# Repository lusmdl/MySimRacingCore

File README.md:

# Sim Racing Core Controller

Welcome to the Sim Racing Core Controller repository!

This project focuses on programming the ATmega32u4 microcontroller to serve as the core of a high-performance sim racing setup. 
The controller independently handles all tasks, including steering, pedals, and accessory management, ensuring a streamlined and immersive racing experience—all without external setup software.

Other projects require PC-based software. 
This solution does everything directly on the microcontroller. 
Sensor calibration, configuration, and adjustments are all handled locally and stored in the microcontroller’s memory. 
The system can be operated intuitively via a simple interface.

This repository is designed to prioritize simplicity and reliability, with clean, maintainable code that’s easy to understand and adapt to your needs.

## Features

- 32 buttons (includes joystick button (1) for setup)
- Steering-Axis without FFB (Steering)
- Accelerate-Axis
- Brake-Axis
- X-Rotation-Axis (Joystick)
- Y-Rotation-Axis (Joystick)

## Getting Started

### Hardware Requirements

- **ATmega32u4 Microcontroller**: I use the original arduino micro board
- **Steering Wheel**: I use a cheap optical encoder with A and B line from china
- **Pedals**: I use a old xbox360 racing wheel pedal set. It only needs to work with potis.
- **Buttons**: The microcontroller get the 16 bit data from I2C Interface Adress 8 & 9 button data. You need a diffrent device for this. Look at my other project [here](https://github.com/lusmdl/MySimRacingButtonBox)!
- **Joystick**: I use a "normal" joystick from the Sony DualShock series and have designed a custom PCB to integrate it seamlessly. Special thanks to [little-scale](https://github.com/little-scale) for providing the [PS4 joystick footprint](https://github.com/little-scale/PS4_joystick_footprint), which served as the foundation for my design.
- **LCD**: I use a Arduino Uno with a LCD 2x16 shield. Look at this project [here](https://github.com/lusmdl/MySimRacingSetupDisplay).

> Example PCBs for this project

### Software Requirements

- [**Platform IO**](https://platformio.org/install/ide?install=vscode): Used for programming the ATmega32u4 microcontroller.
- [**AVR Lib**](https://github.com/avrdudes/avr-libc.git): standard lib for programming atmega microcontrollers with platformIO.
- [**Arduino AVR Core**](https://github.com/arduino/ArduinoCore-avr.git): used `Arduino.h`, `Wire.h` and `EEPROM.h`
- [**Arduino Joystick With Force Feedback Library**](https://github.com/YukMingLaw/ArduinoJoystickWithFFBLibrary.git): used for USB communication with the game

### Software Installation and Setup

> You can use the pre compiled hex file. Or you compile it yourself.

1. **Install PlatformIO**:
- Follow the [installation guide](https://platformio.org/install) to set up PlatformIO in your preferred environment (VSCode, Atom, etc.).

2. **Clone the Repository**:

```sh
git clone https://github.com/lusmdl/MySimRacingCore.git
```

3. **Open the Project**:
- Open the cloned repository folder in your PlatformIO environment.

4. **Build and Upload**:
- Connect your Arduino Micro.
- Build and upload the code using PlatformIO:

```sh
pio run --target upload
```

### Hardware Setup

To get started, you’ll need to assemble the accessories and adapt them to the Arduino Micro.

Special attention is required for the I2C interface and the encoder, as proper pull-up resistors are essential for reliable operation. 
To simplify this process, I’ve designed a custom PCB that integrates the Arduino Micro with all necessary accessories and I2C clients.

## Usage

1. **Connecting the Hardware**:
- Connect the accessorys to the Arduino Micro as per your configuration.
- Connect the Arduino Micro to the PC.

2. **Running the Code**:
- Power up your setup.
- The Arduino Micro will continuously push the accessorys states and update the Game data via USB.

3. **Setup the Wheelebase**
- Hit the joystick butten while booting..
- follow the instructions on the lcd

4. **Start your game and try it**

5. **Give feedback and report bugs**

## Documentation
- **Software**: [doc/software/html/index.html](/doc/software/html/index.html)

## Contributing

We welcome contributions from the community!

First, read the [general contributing conventions for projects from me](CONTRIBUTING.md).

1. Fork the repository.
2. Create a new branch (`git checkout -b feature-branch`).
3. Commit your changes (`git commit -am 'Add new feature'`).
4. Push to the branch (`git push origin feature-branch`).
5. Create a new Pull Request.

## License

This project is licensed under the MIT License - see the [LICENSE](LICENSE) file for details.

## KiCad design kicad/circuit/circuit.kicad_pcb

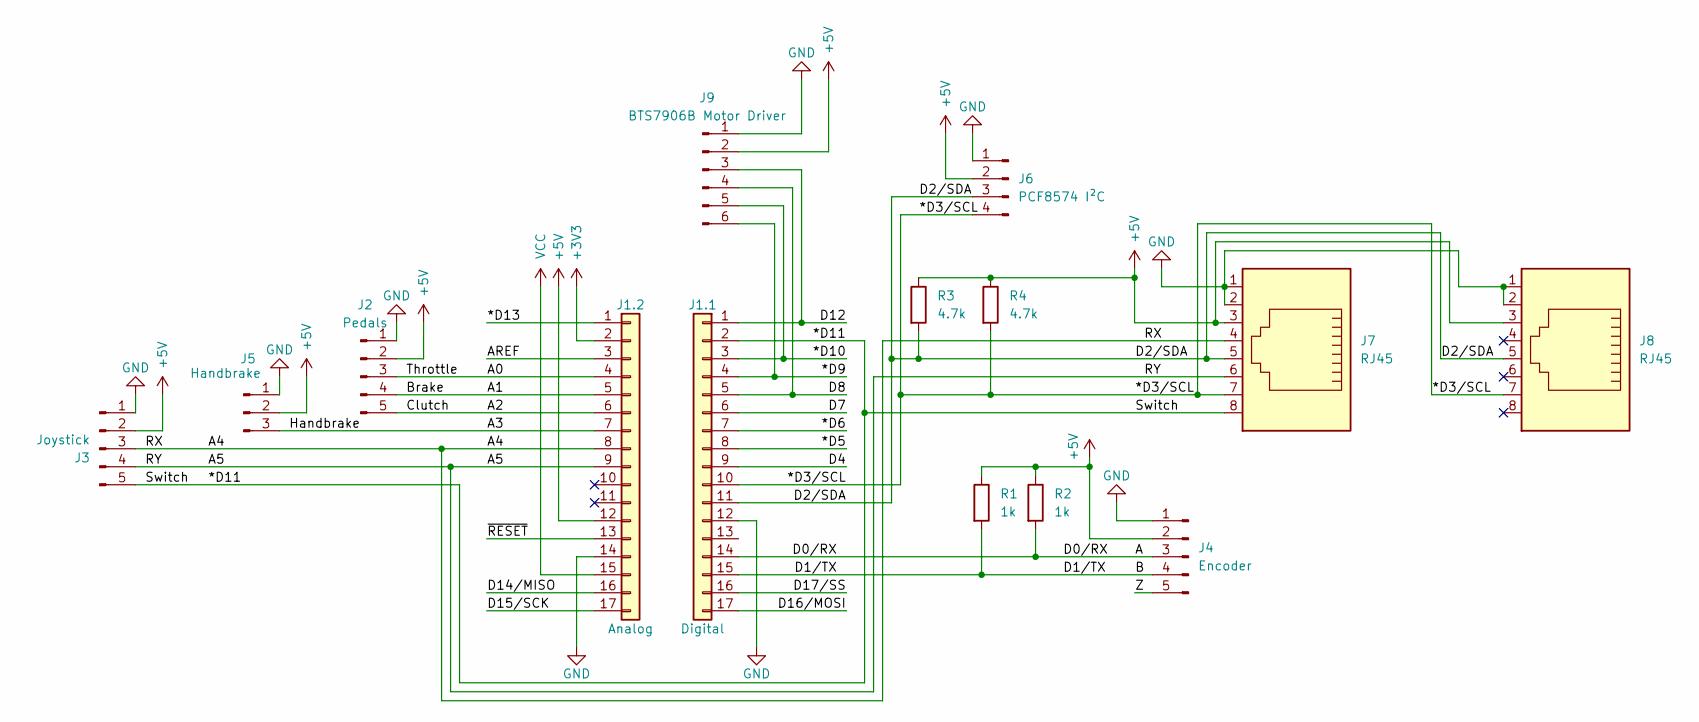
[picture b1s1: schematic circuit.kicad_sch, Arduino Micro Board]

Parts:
J1.1: Digital; PinSocket_1x17_P2.54mm_Vertical_SMD_Pin1Left
J1.2: Analog; PinSocket_1x17_P2.54mm_Vertical_SMD_Pin1Left
J2: Pedals; PinHeader_2x03_P2.54mm_Vertical_SMD
J3: Joystick; PinHeader_2x03_P2.54mm_Vertical_SMD
J4: Encoder; PinHeader_2x03_P2.54mm_Vertical_SMD
J5: Handbrake; PinHeader_2x02_P2.54mm_Vertical_SMD
J6: PCF8574 I²C; PinHeader_2x02_P2.54mm_Vertical_SMD
J7, J8: RJ45; RJ45_Molex_0855135013_Vertical
J9: BTS7906B Motor Driver; PinHeader_2x03_P2.54mm_Vertical_SMD
R1, R2: 1k; R_0402_1005Metric
R3, R4: 4.7k; R_0402_1005Metric

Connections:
+3V3: J1.2.2
+5V: J1.2.12, J2.2, J3.2, J4.2, J5.2, J6.2, J7.3, J8.3, J9.2, R1.1, R2.1, R3.1, R4.1
/*D3/SCL: J1.1.10, J6.4, J7.7, J8.7, R4.2
/*D5: J1.1.8
/*D6: J1.1.7
/*D9: J1.1.4, J9.6
/*D10: J1.1.3, J9.5
/*D11: J1.1.2, J3.5, J7.8
/*D13: J1.2.1
/A: J1.1.14, J4.3, R2.2
/A0: J1.2.4, J2.3
/A1: J1.2.5, J2.4
/A2: J1.2.6, J2.5
/A3: J1.2.7, J5.3
/A4: J1.2.8, J3.3, J7.4
/A5: J1.2.9, J3.4, J7.6
/AREF: J1.2.3
/B: J1.1.15, J4.4, R1.2
/D2/SDA: J1.1.11, J6.3, J7.5, J8.5, R3.2
/D4: J1.1.9
/D7: J1.1.6
/D8: J1.1.5, J9.4
/D12: J1.1.1, J9.3
/D14/MISO: J1.2.16
/D15/SCK: J1.2.17
/D16/MOSI: J1.1.17
/D17/SS: J1.1.16
/Z: J4.5
/~RESET: J1.2.13
GND: J1.1.12, J1.2.14, J2.1, J3.1, J4.1, J5.1, J6.1, J7.1, J7.2, J8.1, J8.2, J9.1
VCC: J1.2.15

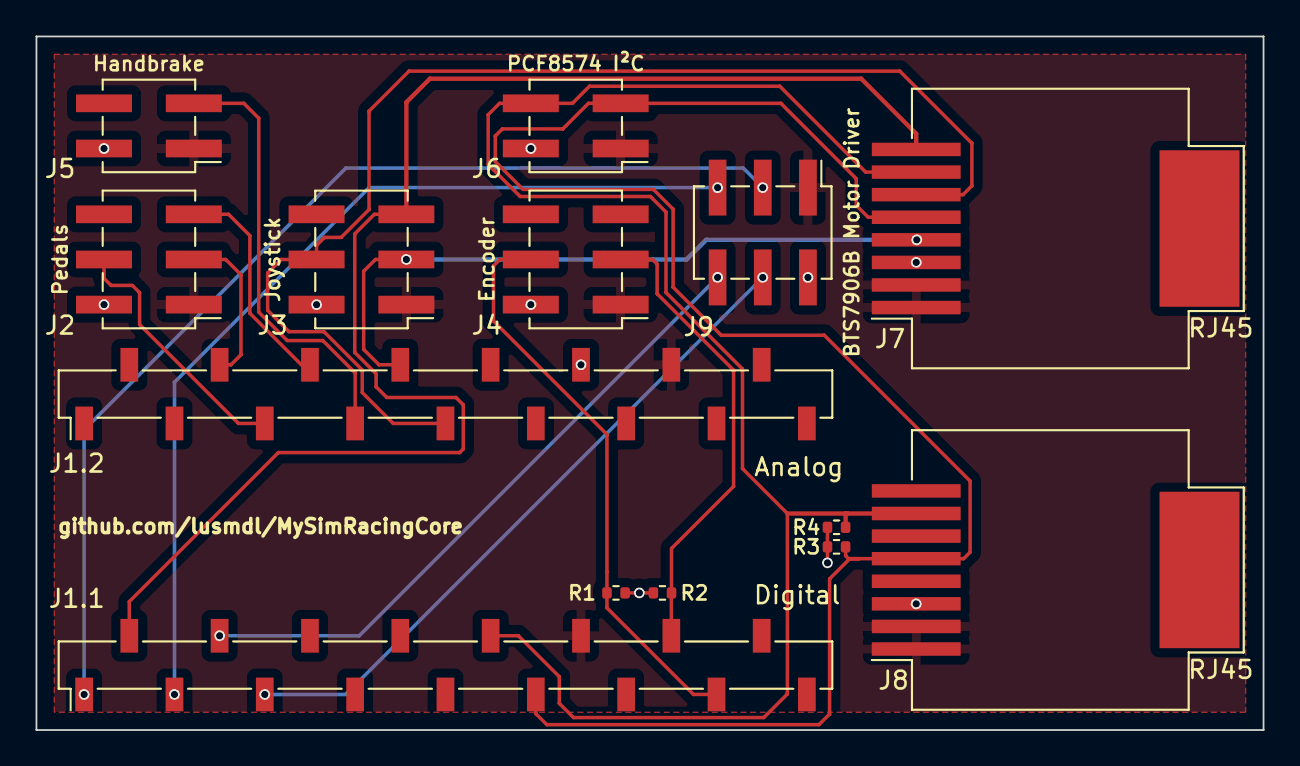
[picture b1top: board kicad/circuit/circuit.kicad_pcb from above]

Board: 2 copper layers, 69.0 x 39.0 mm, 14 parts (0 on the bottom side), 17 nets.

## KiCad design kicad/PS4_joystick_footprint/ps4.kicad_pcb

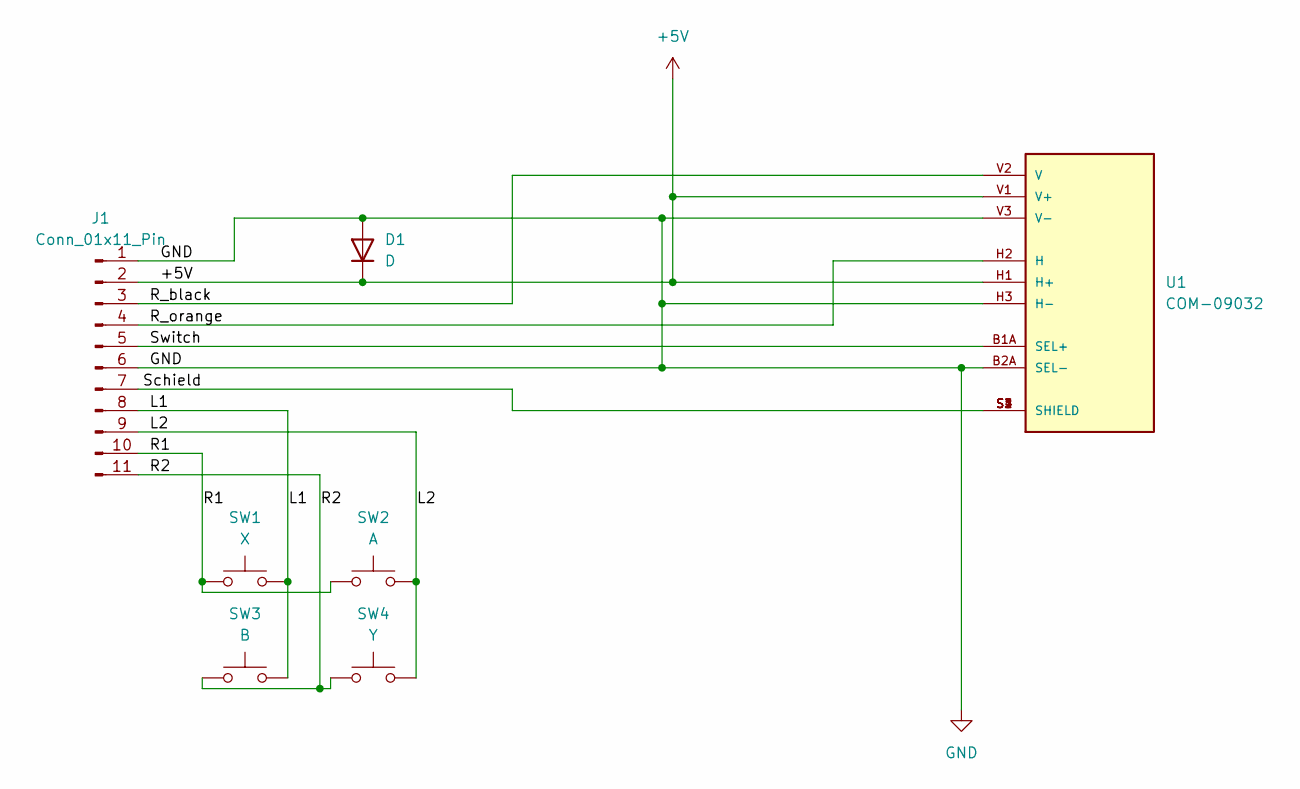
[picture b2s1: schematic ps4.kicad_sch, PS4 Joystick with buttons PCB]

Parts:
D1: D; D_MiniMELF
J1: Conn_01x11_Pin; PinHeader_1x11_P2.54mm_Vertical
SW1: X; SW_SPST_B3S-1000
SW2: A; SW_SPST_B3S-1000
SW3: B; SW_SPST_B3S-1000
SW4: Y; SW_SPST_B3S-1000
U1: COM-09032; PS4_joystick; PARTREV N/A

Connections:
+5V: D1.1 (K), J1.2, U1.H1 (H+), U1.V1 (V+)
/L1: J1.8, SW1.2, SW3.2
/L2: J1.9, SW2.2, SW4.2
/R1: J1.10, SW1.1, SW2.1
/R2: J1.11, SW3.1, SW4.1
/R_black: J1.3, U1.V2 (V)
/R_orange: J1.4, U1.H2 (H)
/Schield: J1.7, U1.S1 (SHIELD), U1.S2 (SHIELD), U1.S3 (SHIELD), U1.S4 (SHIELD)
/Switch: J1.5, U1.B1A (SEL+)
GND: D1.2 (A), J1.1, J1.6, U1.B2A (SEL-), U1.H3 (H-), U1.V3 (V-)

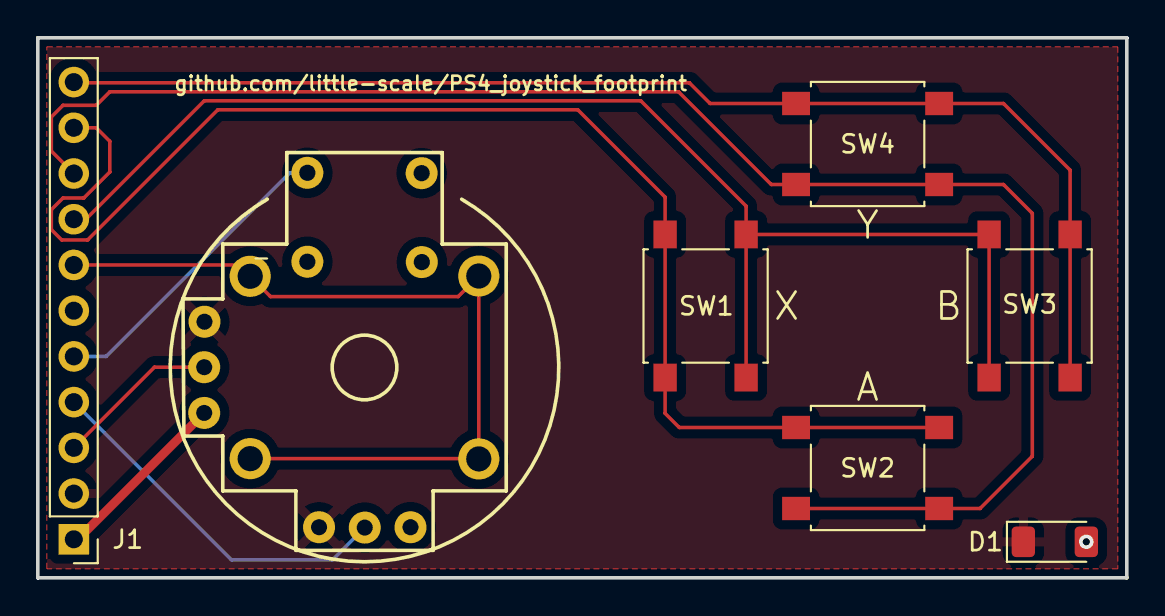
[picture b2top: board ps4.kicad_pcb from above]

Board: 2 copper layers, 60.5 x 30.0 mm, 7 parts (0 on the bottom side), 10 nets.

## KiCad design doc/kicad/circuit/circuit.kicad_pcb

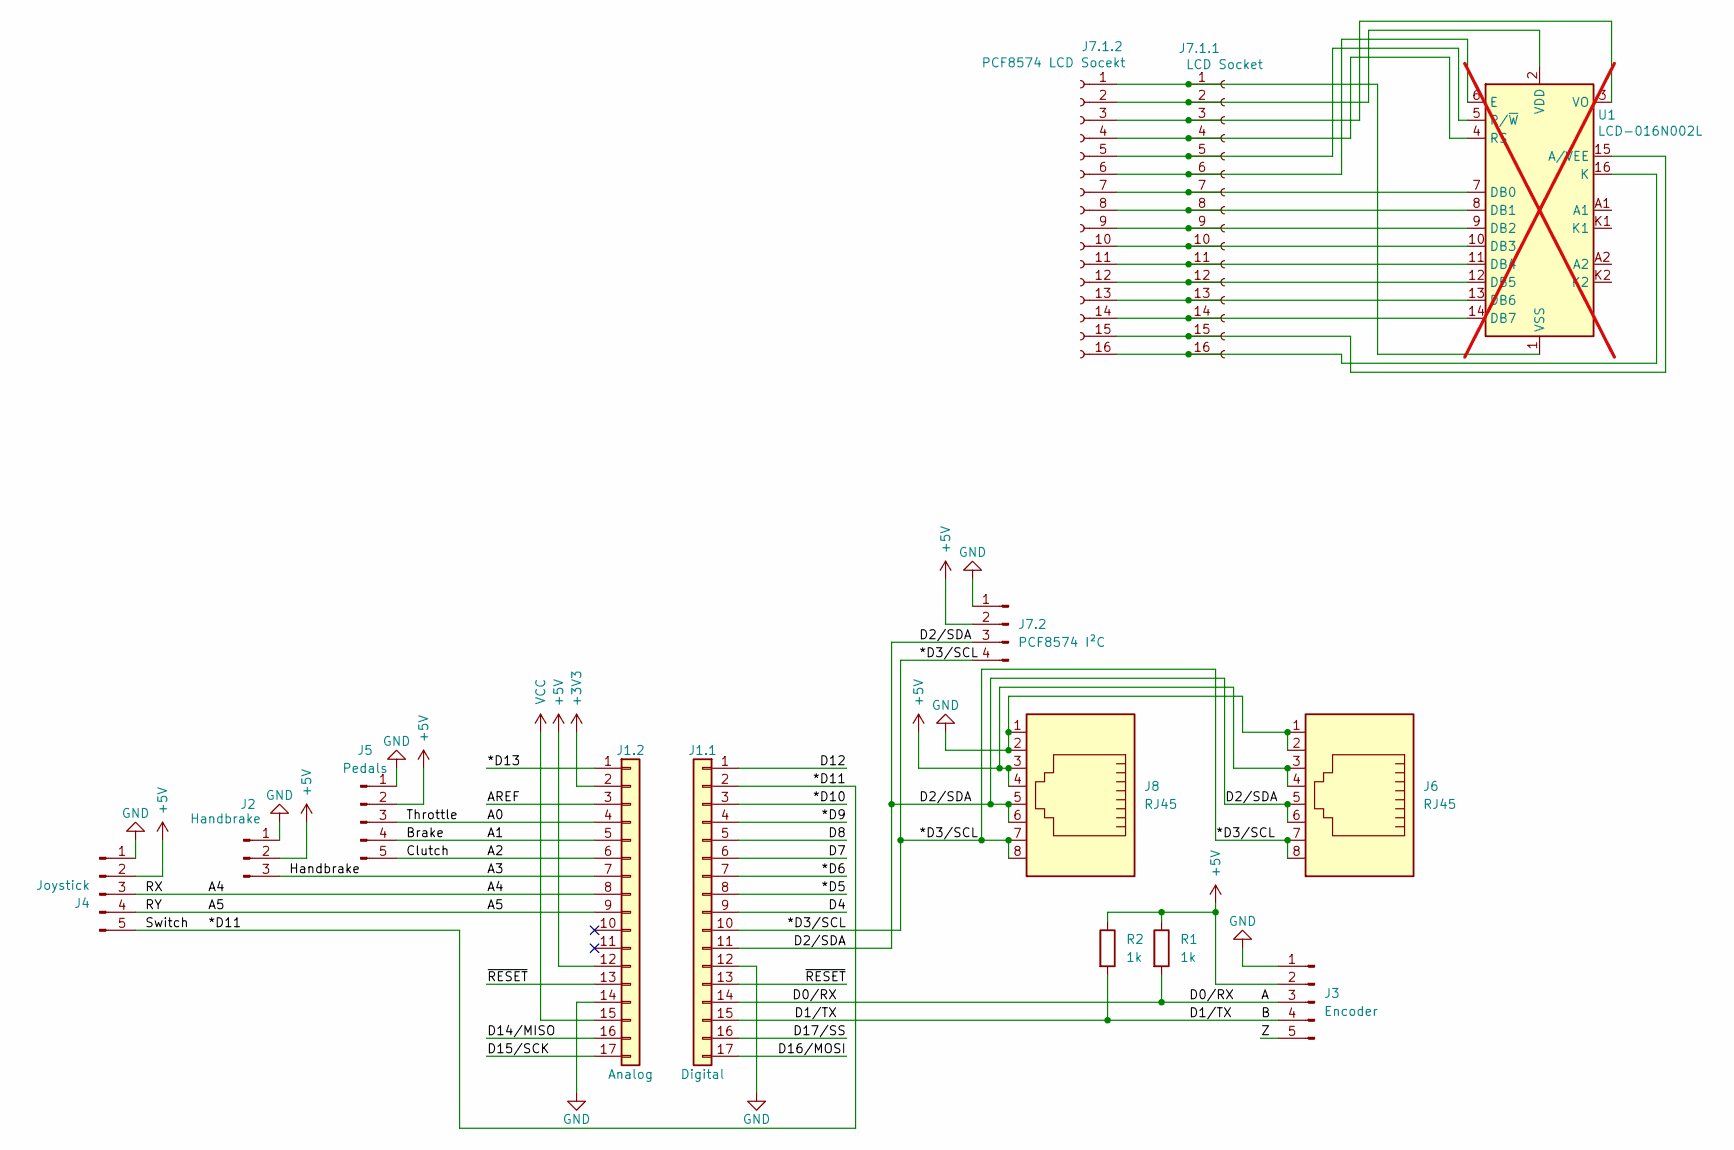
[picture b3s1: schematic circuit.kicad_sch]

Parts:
J1.1: Digital; PinSocket_1x17_P2.54mm_Vertical_SMD_Pin1Left
J1.2: Analog; PinSocket_1x17_P2.54mm_Vertical_SMD_Pin1Left
J2: Handbrake; PinHeader_1x03_P2.54mm_Vertical_SMD_Pin1Left
J3: Encoder; PinHeader_1x05_P2.54mm_Vertical_SMD_Pin1Left
J4: Joystick; PinHeader_1x05_P2.54mm_Vertical_SMD_Pin1Left
J5: Pedals; PinHeader_1x05_P2.54mm_Vertical_SMD_Pin1Left
J6, J8: RJ45; RJ45_Molex_0855135013_Vertical
J7.1.1: LCD Socket; PinSocket_1x16_P2.54mm_Vertical_SMD_Pin1Left
J7.1.2: PCF8574 LCD Socekt; PinSocket_1x16_P2.54mm_Vertical_SMD_Pin1Left
J7.2: PCF8574 I²C; PinHeader_1x04_P2.54mm_Vertical_SMD_Pin1Left
R1, R2: 1k; R_0805_2012Metric_Pad1.20x1.40mm_HandSolder
U1: LCD-016N002L; not fitted

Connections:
+3V3: J1.2.2
+5V: J1.2.12, J2.2, J3.2, J4.2, J5.2, J6.3, J6.4, J7.2.2, J8.3, J8.4, R1.1, R2.1
/*D3/SCL: J1.1.10, J6.7, J6.8, J7.2.4, J8.7, J8.8
/*D5: J1.1.8
/*D6: J1.1.7
/*D9: J1.1.4
/*D10: J1.1.3
/*D11: J1.1.2, J4.5
/*D13: J1.2.1
/A: J1.1.14, J3.3, R1.2
/A0: J1.2.4, J5.3
/A1: J1.2.5, J5.4
/A2: J1.2.6, J5.5
/A3: J1.2.7, J2.3
/A4: J1.2.8, J4.3
/A5: J1.2.9, J4.4
/AREF: J1.2.3
/B: J1.1.15, J3.4, R2.2
/D2/SDA: J1.1.11, J6.5, J6.6, J7.2.3, J8.5, J8.6
/D4: J1.1.9
/D7: J1.1.6
/D8: J1.1.5
/D12: J1.1.1
/D14/MISO: J1.2.16
/D15/SCK: J1.2.17
/D16/MOSI: J1.1.17
/D17/SS: J1.1.16
/Z: J3.5
/~RESET: J1.1.13, J1.2.13; also elsewhere on the board
GND: J1.1.12, J1.2.14, J2.1, J3.1, J4.1, J5.1, J6.1, J6.2, J7.2.1, J8.1, J8.2; also elsewhere on the board
unnamed: J7.1.1.1, J7.1.2.1, U1.1 (VSS)
unnamed: J7.1.1.2, J7.1.2.2, U1.2 (VDD)
unnamed: J7.1.1.3, J7.1.2.3, U1.3 (VO)
unnamed: J7.1.1.4, J7.1.2.4, U1.4 (RS)
unnamed: J7.1.1.5, J7.1.2.5, U1.5 (R/~W)
unnamed: J7.1.1.6, J7.1.2.6, U1.6 (E)
unnamed: J7.1.1.7, J7.1.2.7, U1.7 (DB0)
unnamed: J7.1.1.8, J7.1.2.8, U1.8 (DB1)
unnamed: J7.1.1.9, J7.1.2.9, U1.9 (DB2)
unnamed: J7.1.1.10, J7.1.2.10, U1.10 (DB3)
unnamed: J7.1.1.11, J7.1.2.11, U1.11 (DB4)
unnamed: J7.1.1.12, J7.1.2.12, U1.12 (DB5)
unnamed: J7.1.1.13, J7.1.2.13, U1.13 (DB6)
unnamed: J7.1.1.14, J7.1.2.14, U1.14 (DB7)
unnamed: J7.1.1.15, J7.1.2.15, U1.15 (A/VEE)
unnamed: J7.1.1.16, J7.1.2.16, U1.16 (K)
VCC: J1.2.15

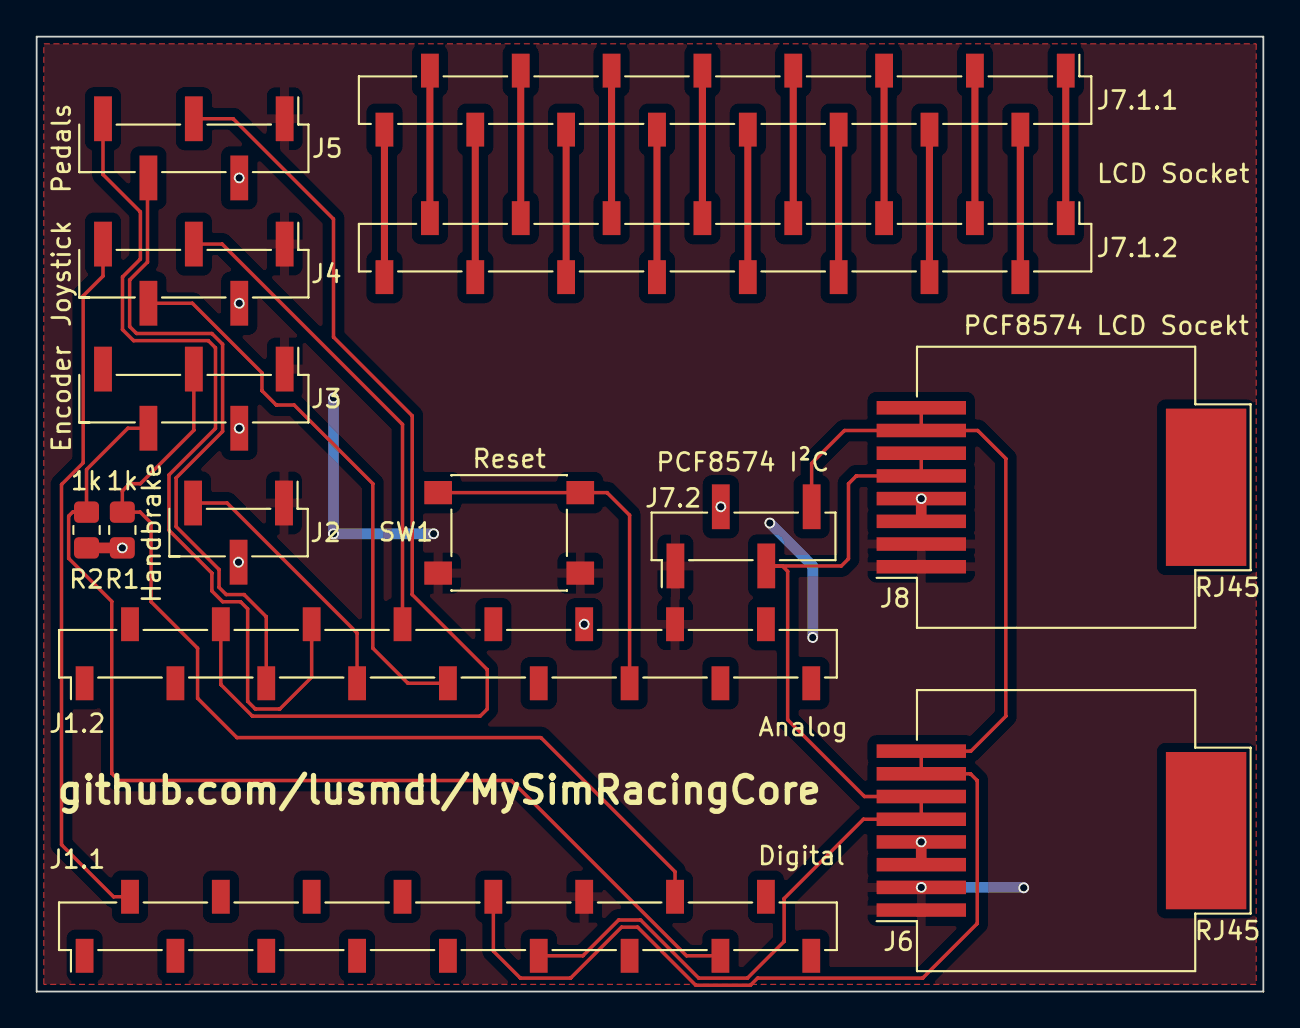
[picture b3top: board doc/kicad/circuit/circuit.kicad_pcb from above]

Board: 2 copper layers, 68.6 x 53.4 mm, 14 parts (0 on the bottom side), 30 nets.

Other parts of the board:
SW1: Reset; SW_Push_1P1T_NO_6x6mm_H9.5mm

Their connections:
/~RESET: SW1.2; also elsewhere on the board
GND: SW1.1; also elsewhere on the board

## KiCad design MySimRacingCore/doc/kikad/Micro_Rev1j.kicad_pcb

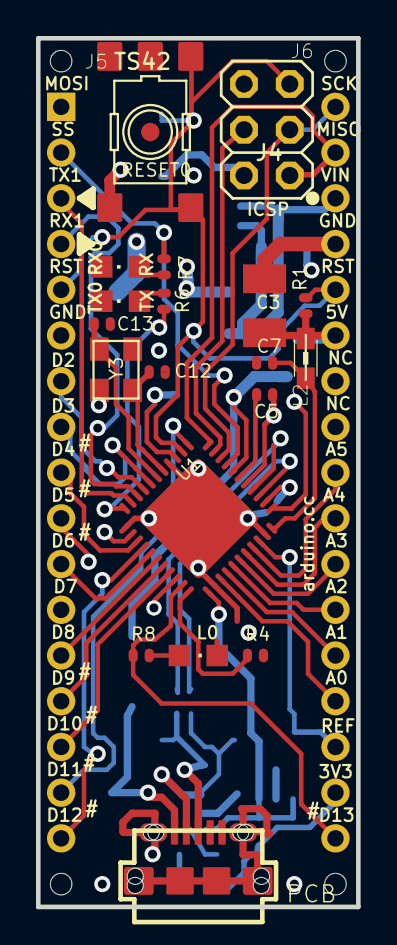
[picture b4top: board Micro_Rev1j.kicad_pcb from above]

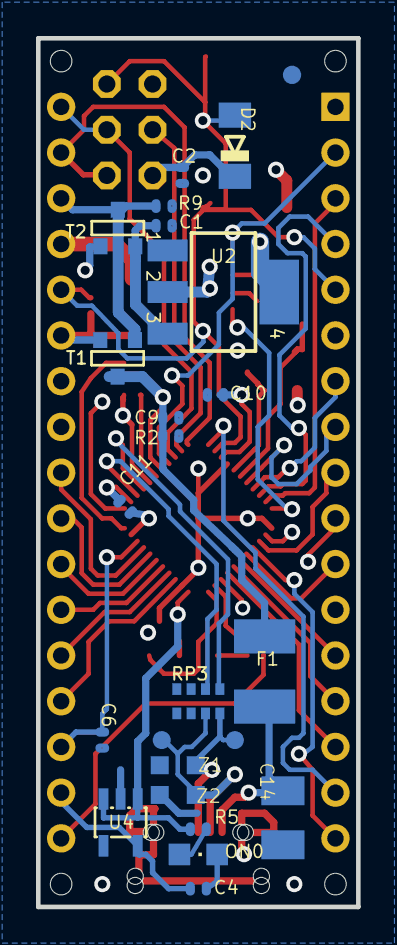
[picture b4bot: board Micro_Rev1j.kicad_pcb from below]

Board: 4 copper layers, 17.8 x 48.3 mm, 51 parts (22 on the bottom side), 47 nets.

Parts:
@HOLE0, @HOLE1, @HOLE2, @HOLE3: (no value)
C1, C2, C6, C9, C10, C11: 100n; C0402
C3, C14: 22u; SMC_B
C4, C5, C7: 1uF; C0402
C12, C13: 22pF; C0402
D2: CD1206-S01575; MINIMELF
D+0: DNP; TP-1.00MM
D-0: DNP; TP-1.00MM
F1: MF-MSMF050-2 500mA; L1812
FRAME1: DNP; FRAME
J3: USB Micro; CON2_USB_MICRO_B_AT
J4: 3x2M; 2X03
J5: HEAD17-NOSS
J6: HEAD17-NOSS-1
L0: green; CHIPLED_0805
L2: MH2029-300Y; 0805
ON0: blue; CHIPLED_0805
R1, R2, R4, R9: 10K; R0402
R5, R6, R7, R8: 1K; R0402
RESET0: TS42
RP3: 22R; CAY16
RX0: yellow; CHIPLED_0805
T1: FDN340P/PMV48XP; SOT-23
T2: PMV48XP; SOT-23
TX0: yellow; CHIPLED_0805
U1: ATMEGA32U4-XUMU; QFN44ML7X7
U2: NCP1117-5; SOT223
U4: LP2985-33DBVR; SOT23-DBV
U$37, U$53: DNP; FD-1-1.5
Y3: 16MHz KX-7; CRYSTAL-3.2-2.5
Z1, Z2: CG0603MLC-05E; CT_CN0603

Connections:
3V3: C4.1, J6.16, U4.5
+5V: C2.1, C3.+, C10.1, C11.1, D2.C, J4.2, J6.6, L2.1, R1.1, R5.1, T1.2, T2.3, U1.2, U1.14, U1.24, U1.34, U2.2, U2.4, U4.1, U4.3
+VIN: C1.1, T2.2, U2.3
A0: J6.14, U1.36
A1: J6.13, U1.37
A2: J6.12, U1.38
A3: J6.11, U1.39
A4: J6.10, U1.40
A5: J6.9, U1.41
AREF: C6.1, J6.15, U1.42
AVCC: C7.1, L2.2, U1.44
D0/RX: J5.4, U1.20
D1/TX: J5.3, U1.21
D2/SDA: J5.7, U1.19
D3/SCL: J5.8, U1.18
D4*: J5.9, U1.25
D5*: J5.10, U1.31
D6*: J5.11, U1.27
D7: J5.12, U1.1
D+: D+0.X, J3.P3, RP3.8, Z1.1
D-: D-0.X, J3.P2, RP3.7, Z2.1
GND: C1.2, C2.2, C3.-, C4.2, C5.2, C6.2, C7.2, C9.2, C10.2, C11.2, C12.1, C13.1, C14.-, J3.P5, J3.S1, J3.S2, J3.S3, J3.S4, J3.S5, J3.S6, J4.6, J5.6, J6.4, L0.C, ON0.C, R2.1, R4.2, R9.1, RESET0.3, RESET0.4, RESET0.5, RP3.3, RP3.4, RP3.5, RP3.6, RX0.C, TX0.C, U1.5, U1.15, U1.23, U1.35, U1.43, U1.EXP, U2.1, U4.2, Y3.2, Y3.4, Z1.2, Z2.2
HWB: R4.1, U1.33
IO8: J5.13, U1.28
IO9*: J5.14, U1.29
IO10*: J5.15, U1.30
IO11*: J5.16, U1.12
IO12*: J5.17, U1.26
IO13*: J6.17, R8.1, U1.32
MISO: J4.1, J6.2, U1.11
MOSI: J4.4, J5.1, U1.10
unnamed: R7.2, RX0.A
unnamed: ON0.A, R5.2
unnamed: R6.2, TX0.A
unnamed: L0.A, R8.2
RD+: RP3.1, U1.4
RD-: RP3.2, U1.3
RESET: D2.A, J4.5, J5.5, J6.5, R1.2, RESET0.1, RESET0.2, U1.13
RXLED/SS: J5.2, R7.1, U1.8
SCK: J4.3, J6.1, U1.9
TXLED: R6.1, U1.22
UCAP: C5.1, U1.6
VIN: J6.3, R9.2, T1.3, T2.1
VUSB: C9.1, F1.2, R2.2, T1.1, U1.7
VUSBD: C14.+, F1.1, J3.P1
XTAL1: C13.2, U1.17, Y3.3
XTAL2: C12.2, U1.16, Y3.1

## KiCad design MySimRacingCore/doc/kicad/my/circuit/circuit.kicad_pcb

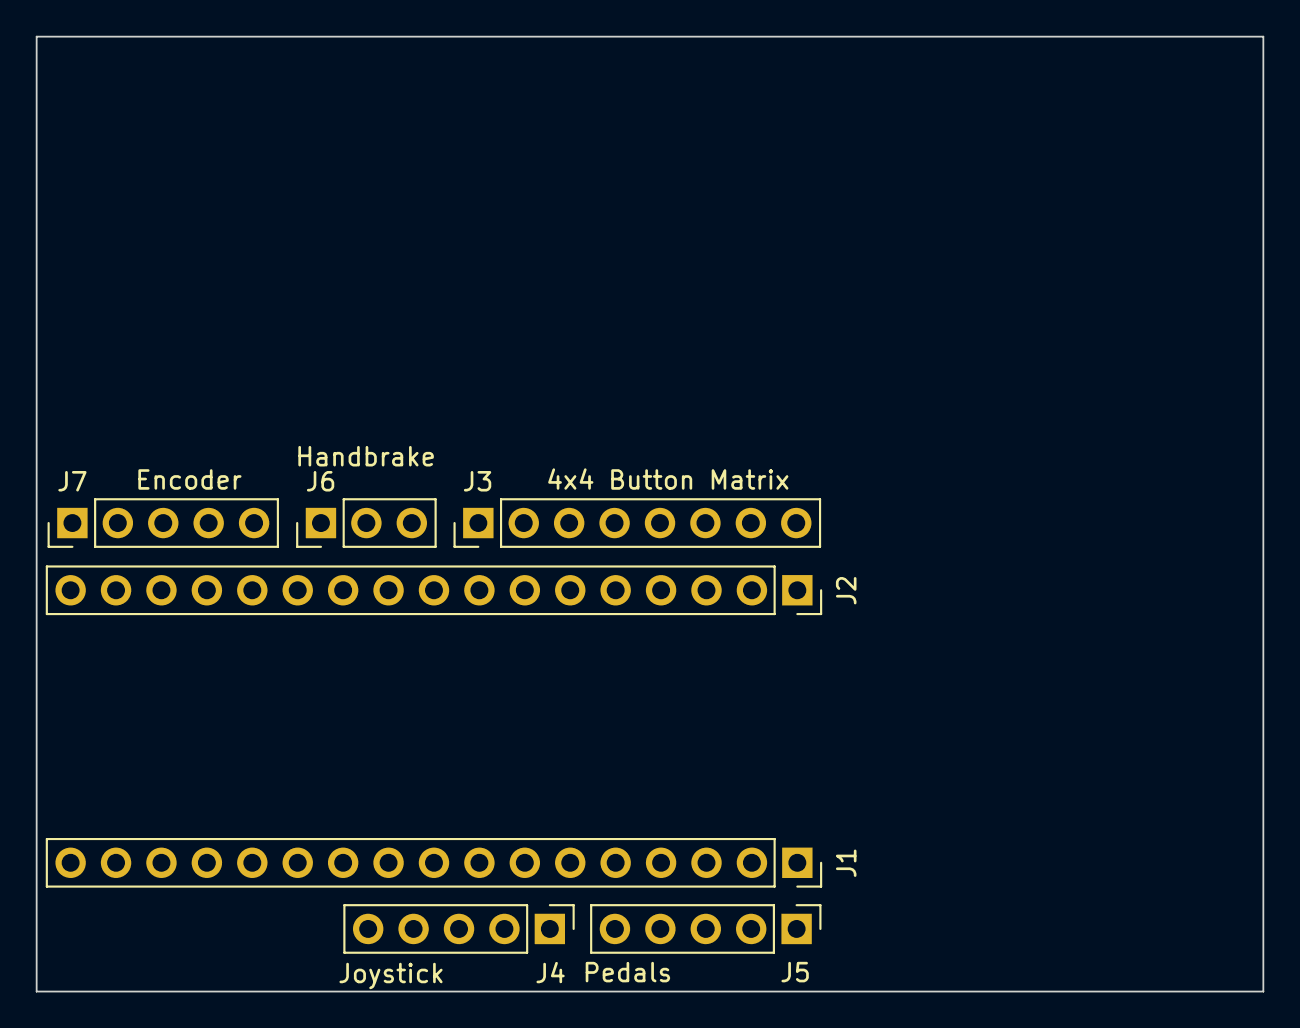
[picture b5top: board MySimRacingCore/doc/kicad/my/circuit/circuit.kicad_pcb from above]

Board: 2 copper layers, 68.6 x 53.4 mm, 7 parts (0 on the bottom side), 19 nets, no tracks yet.

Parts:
J1: Analog; PinSocket_1x17_P2.54mm_Vertical
J2: Digital; PinSocket_1x17_P2.54mm_Vertical
J3: 4x4 Button Matrix; PinHeader_1x08_P2.54mm_Vertical
J4: Joystick; PinHeader_1x05_P2.54mm_Vertical
J5: Pedals; PinHeader_1x05_P2.54mm_Vertical
J6: Handbrake; PinHeader_1x03_P2.54mm_Vertical
J7: Encoder; PinHeader_1x05_P2.54mm_Vertical

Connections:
+5V: J1.12, J4.2, J5.2, J6.2, J7.4
/*D5: J2.8, J3.1
/*D6: J2.7, J3.2
/A: J2.14, J7.3
/A0: J1.4, J5.3
/A1: J1.5, J5.4
/A2: J1.6, J5.5
/A3: J1.7, J6.3
/A4: J1.8, J4.3
/A5: J1.9, J4.4
/B: J2.15, J7.2
/D4: J2.9, J3.8
/D7: J2.6, J3.3
/D12: J2.1, J3.4
/D14/MISO: J1.16, J3.5
/D15/SCK: J1.17, J3.6
/D16/MOSI: J2.17, J3.7
/~RESET: J1.13, J2.13
GND: J1.14, J2.12, J4.1, J4.5, J5.1, J6.1, J7.5

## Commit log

2024-07-08 init platform io
2024-07-09 first try
2024-07-09 configure controller communication
2024-07-09 reorder the files and add buttons class
2024-07-09 add code for button matrix. This needs to be tested!
2024-07-10 use keypad.h lib for the buttons.
2024-07-10 some work to do!
2024-07-11 buttons finaly works
2024-07-11 little update
2024-07-11 README.md aktualisieren
2024-07-11 add encoder (not tested)
2024-07-11 update comments
2024-07-13 add some comments and joystick stuff
2024-07-14 implement the joystick axis, the joystick button is still missing. But the axis works
2024-07-14 add kicad project
2024-07-15 add display class
2024-07-15 add new project because i want to handle the 16 buttons with an other microcontroller
2024-07-15 switch back
2024-07-15 fix joystick button
2024-07-15 new folder name
2024-07-15 refactoring for twi buttons
2024-07-15 make the code lightweigth
2024-07-16 change the circuit
2024-07-19 start with setup lcd
2024-07-19 add setup for Rotary axis (x and y)
2024-07-19 add some encoder stuff
2024-07-20 implement encoder set zero
2024-07-21 implement encoder
2024-07-21 start with eeprom
2024-07-21 fix EEPROM object
2024-07-21 platformio.ini aktualisieren
2024-07-22 eeprom works
2024-07-22 fix encoder degree. but have issue with exit assetto corsa -> it will not close
2024-07-23 implement a fast/normal/slow task management in main.cpp
2024-07-23 add pedals
2024-07-23 add next i2c button box connector
2024-07-23 fix issue with cycle counter
2024-07-23 issue with encoder
2024-07-23 encoder works, but it´s pretty ugly. need to refactor it
2024-07-23 little adjustment
2024-09-08 refactoring
2024-12-21 finish layout the PCB
2024-12-21 finish PCBA
2024-12-21 export schematics
2024-12-23 generate doc
2024-12-23 update contributing
2024-12-25 remove lcd and add gitignore for kicad
2024-12-25 update gitignore
2024-12-25 update pcba picture
2024-12-26 add ps4 joystick pcb + data over rj45
2024-12-26 add picture of joystick pcb
2024-12-26 start to add button matrix to joystick pcb
2024-12-27 update pcb and documentation
2024-12-27 update joystick pcb
2024-12-27 add little-scale/PS4_joystick_footprint next to the footprint
2024-12-29 add force feedback device to layout
2025-01-14 update Fertigungsdaten
2025-01-14 compile firmware
2025-01-16 add rj45 datasheet
2025-01-19 add lib
2025-02-07 upload real pcba picture
2025-03-22 fix: all 32 button works
2025-03-22 setup timer 3 for receiving data
2025-03-22 implement smooth method for joystick
2025-03-25 implement tolerance calculation for break and throttle
2025-03-25 fix issue with display and encoder
2025-03-25 change setup routine
2025-03-25 return to non corrected joystick
2025-03-25 try to center the joysticks
2025-03-25 clean code
2025-03-26 i have a stack overflow issue above 2140 bytes of RAM
2025-03-30 change Setup routine to a i2c device - saving RAM and FLASH storage
2025-04-03 fix issue with other pcs recognizing the controller
2025-04-03 handle the tolerance setting for the pedals with adc class
2025-04-09 tuning
2025-05-10 optimize ps4 joystick pcb
2025-05-10 generate PCB assembly data for v1.1.0
2025-05-10 update doxygen docs
2025-05-10 regenerate firmware and delete others
